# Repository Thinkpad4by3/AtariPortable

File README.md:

# AtariPortable
Atari 2600 new board with Composite and S-Video

Despite the name, it is not a portable yet. It is a remade board from original Atari 2600 schematics but updated for more modern features like proper composite and s-video outputs. Also Made the board physically smaller.

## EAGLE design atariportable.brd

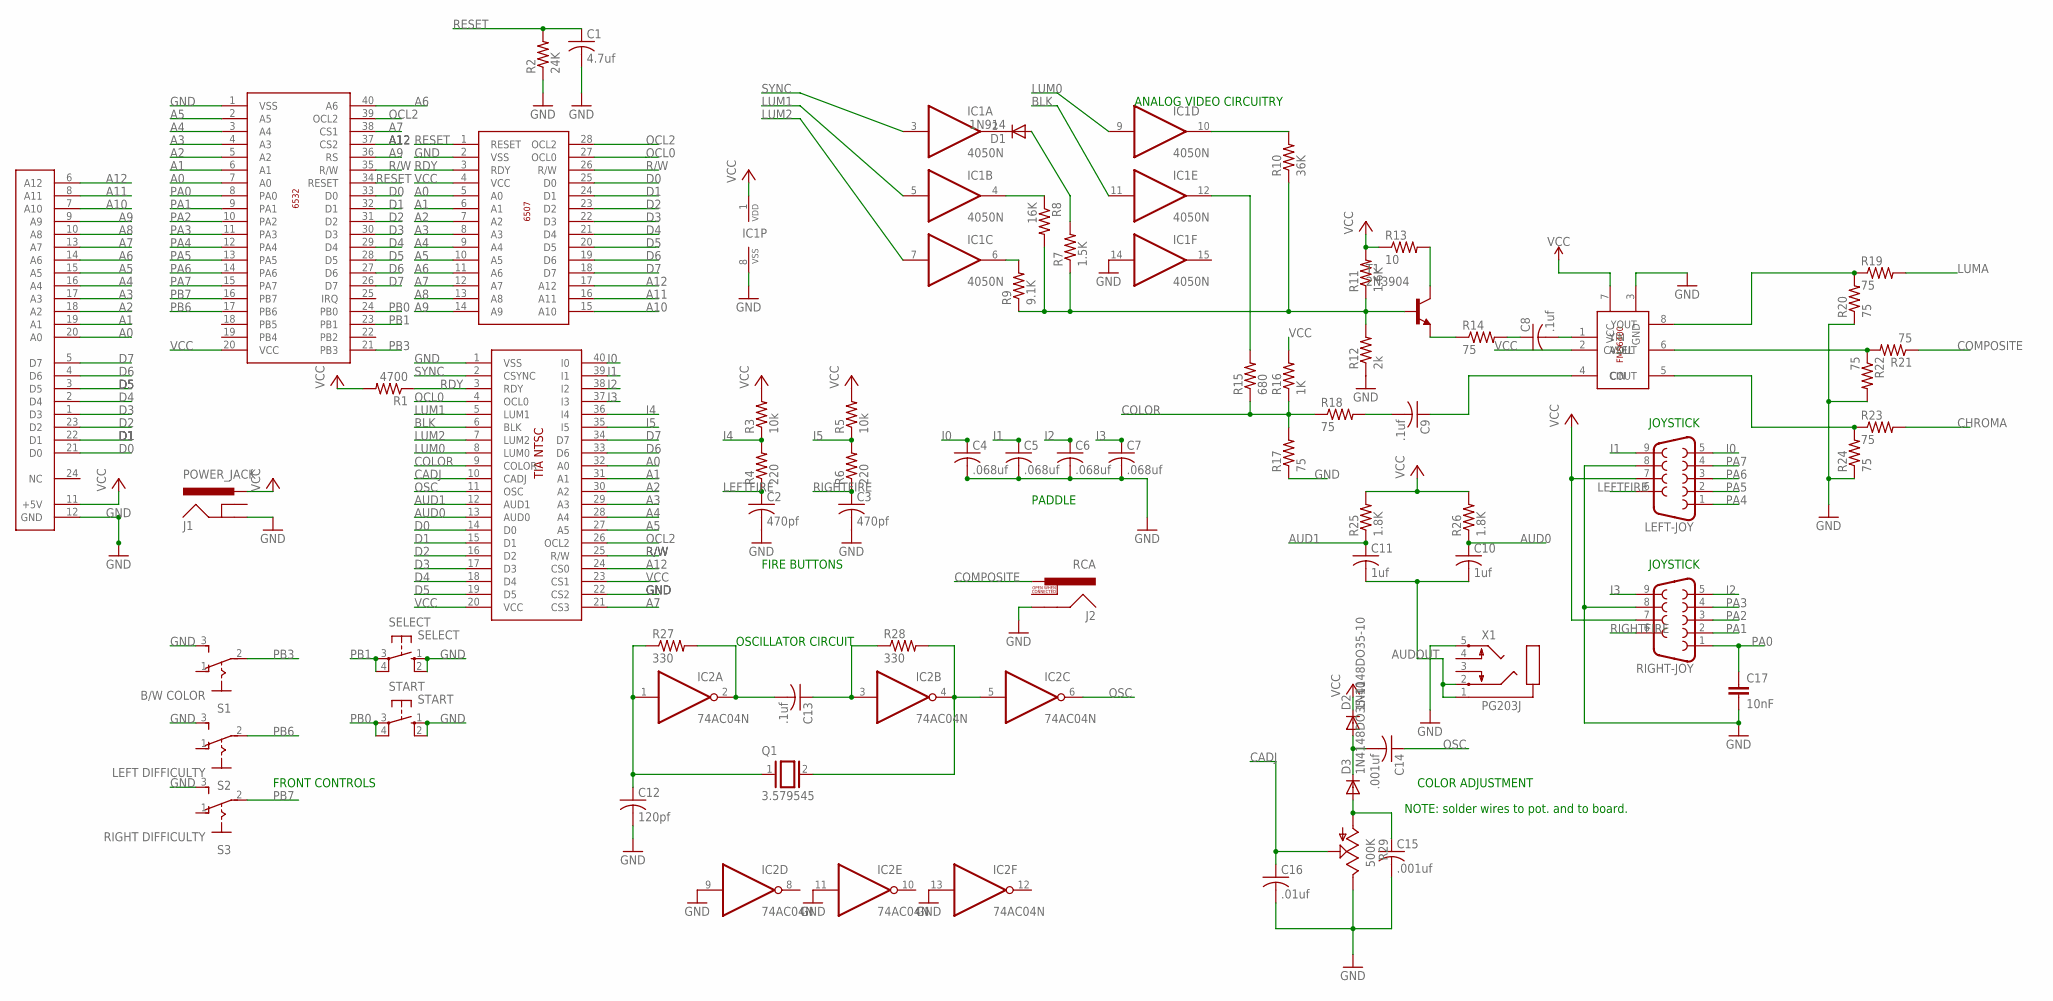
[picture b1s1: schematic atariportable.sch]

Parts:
6507: 6507; DIP28
6532: 6532; DIP40
C1: 4.7uf; C025-030X050
C2, C3: 470pf; C025-050X050
C4, C5, C6, C7: .068uf; C025-024X044
C8, C9: .1uf; C025-025X050
C10, C11: 1uf; C025-050X050
C12: 120pf; C075-042X103
C13: .1uf; C050-050X075
C14, C15: .001uf; C025-050X050
C16: .01uf; C050-055X075
C17: 10nF; C2.5-3
CONN1: 24POSCECARDEDGE; 24POSEDGECARD
D1: 1N914; DO35-10
D2, D3: 1N4148DO35-10; DO35-10
IC1: 4050N; DIL16
IC2: 74AC04N; DIL14
J1: POWER_JACK; POWER_JACK_PTH
J2: RCA
LEFT-JOY: DB9MALE; DB9_MALE
Q1: 3.579545; Q
R1: 4700; 0207/10
R2: 24K; 0207/10
R3, R5: 10k; 0207/10
R4, R6: 220; 0207/10
R7: 1.5K; 0207/10
R8: 16K; 0207/10
R9: 9.1K; 0207/10
R10: 36K; 0207/10
R11: 1.6K; 0207/10
R12: 2k; 0207/10
R13: 10; 0207/10
R14, R17, R18, R19, R20, R21, R22, R23, R24: 75; 0207/10
R15: 680; 0207/10
R16: 1K; 0207/10
R25, R26: 1.8K; 0207/10
R27, R28: 330; 0207/10
R29: 500K; CA6V
RIGHT-JOY: DB9MALE; DB9_MALE
S1: B/W COLOR; M251
S2: LEFT DIFFICULTY; M251
S3: RIGHT DIFFICULTY; M251
SELECT: SELECT; B3F-10XX
START: START; B3F-10XX
T1: 2N3904; TO92
TIA: TIA; DIP40
U$4: FMS6400; SOIC8
X1: PG203J

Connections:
A0: 6507.5 (A0), 6532.7 (A0), CONN1.20 (A0), TIA.32 (A0)
A1: 6507.6 (A1), 6532.6 (A1), CONN1.19 (A1), TIA.31 (A1)
A2: 6507.7 (A2), 6532.5 (A2), CONN1.18 (A2), TIA.30 (A2)
A3: 6507.8 (A3), 6532.4 (A3), CONN1.17 (A3), TIA.29 (A3)
A4: 6507.9 (A4), 6532.3 (A4), CONN1.16 (A4), TIA.28 (A4)
A5: 6507.10 (A5), 6532.2 (A5), CONN1.15 (A5), TIA.27 (A5)
A6: 6507.11 (A6), 6532.40 (A6), CONN1.14 (A6)
A7: 6507.12 (A7), 6532.38 (CS1), CONN1.13 (A7), TIA.21 (CS3)
A8: 6507.13 (A8), CONN1.10 (A8)
A9: 6507.14 (A9), 6532.36 (RS), CONN1.9 (A9)
A10: 6507.15 (A10), CONN1.7 (A10)
A11: 6507.16 (A11), CONN1.8 (A11)
A12: 6507.17 (A12), 6532.37 (CS2), CONN1.6 (A12), TIA.24 (CS0)
AUD0: C10.1, R26.1, TIA.13 (AUD0)
AUD1: C11.1, R25.1, TIA.12 (AUD1)
AUDOUT: C10.2, C11.2, X1.1, X1.2
BLK: IC1.11 (I), TIA.6 (BLK)
CADJ: C16.1, R29.S, TIA.10 (CADJ)
CHROMA: R23.2
COLOR: R15.1, R16.1, R17.2, R18.1, TIA.9 (COLOR)
COMPOSITE: J2.PIN, R21.1
D0: 6507.25 (D0), 6532.33 (D0), CONN1.21 (D0), TIA.14 (D0)
D1: 6507.24 (D1), 6532.32 (D1), CONN1.22 (D1), TIA.15 (D1)
D2: 6507.23 (D2), 6532.31 (D2), CONN1.23 (D2), TIA.16 (D2)
D3: 6507.22 (D3), 6532.30 (D3), CONN1.1 (D3), TIA.17 (D3)
D4: 6507.21 (D4), 6532.29 (D4), CONN1.2 (D4), TIA.18 (D4)
D5: 6507.20 (D5), 6532.28 (D5), CONN1.3 (D5), TIA.19 (D5)
D6: 6507.19 (D6), 6532.27 (D6), CONN1.4 (D6), TIA.33 (D6)
D7: 6507.18 (D7), 6532.26 (D7), CONN1.5 (D7), TIA.34 (D7)
GND: 6507.2 (VSS), 6532.1 (VSS), C1.2, C2.2, C3.2, C4.2, C5.2, C6.2, C7.2, C12.2, C15.2, C16.2, C17.2, CONN1.12 (GND), IC1.8 (VSS), IC1.14 (I), IC2.7 (GND), IC2.9 (I), IC2.11 (I), IC2.13 (I), J1.GND, J2.SHELL, LEFT-JOY.8, R2.1, R12.1, R17.1, R20.1, R22.2, R24.1, R29.E, RIGHT-JOY.8, S1.3 (S), S2.3 (S), S3.3 (S), SELECT.1 (S), SELECT.2 (S1), START.1 (S), START.2 (S1), TIA.1 (VSS), TIA.22 (CS2), U$4.3 (GND), X1.5
I0: C4.1, LEFT-JOY.5, TIA.40 (I0)
I1: C5.1, LEFT-JOY.9, TIA.39 (I1)
I2: C6.1, RIGHT-JOY.5, TIA.38 (I2)
I3: C7.1, RIGHT-JOY.9, TIA.37 (I3)
I4: R3.1, R4.2, TIA.36 (I4)
I5: R5.1, R6.2, TIA.35 (I5)
LEFTFIRE: C2.1, LEFT-JOY.6, R4.1
LUM0: IC1.9 (I), TIA.8 (LUM0)
LUM1: IC1.5 (I), TIA.5 (LUM1)
LUM2: IC1.7 (I), TIA.7 (LUM2)
LUMA: R19.2
unnamed: D1.C, IC1.2 (O)
unnamed: C8.2, U$4.1 (YIN)
unnamed: D1.A, R7.2
unnamed: IC1.4 (O), R8.1
unnamed: IC1.6 (O), R9.2
unnamed: R7.1, R8.2, R9.1, R10.1, R11.1, R12.2, T1.2 (B)
unnamed: IC1.10 (O), R10.2
unnamed: R13.2, T1.1 (C)
unnamed: R14.1, T1.3 (E)
unnamed: C8.1, R14.2
unnamed: IC1.12 (O), R15.2
unnamed: C9.1, U$4.4 (CIN)
unnamed: C9.2, R18.2
unnamed: R19.1, R20.2, U$4.8 (YOUT)
unnamed: R21.2, R22.1, U$4.6 (CVOUT)
unnamed: R23.1, R24.2, U$4.5 (COUT)
unnamed: C12.1, IC2.1 (I), Q1.1, R27.1
unnamed: C13.2, IC2.2 (O), R27.2
unnamed: C13.1, IC2.3 (I), R28.1
unnamed: IC2.4 (O), IC2.5 (I), Q1.2, R28.2
unnamed: C14.2, D2.A, D3.C
unnamed: C15.1, D3.A, R29.A
OCL0: 6507.27 (OCL0), TIA.4 (OCL0)
OCL2: 6507.28 (OCL2), 6532.39 (OCL2), TIA.26 (OCL2)
OSC: C14.1, IC2.6 (O), TIA.11 (OSC)
PA0: 6532.8 (PA0), C17.1, RIGHT-JOY.1
PA1: 6532.9 (PA1), RIGHT-JOY.2
PA2: 6532.10 (PA2), RIGHT-JOY.3
PA3: 6532.11 (PA3), RIGHT-JOY.4
PA4: 6532.12 (PA4), LEFT-JOY.1
PA5: 6532.13 (PA5), LEFT-JOY.2
PA6: 6532.14 (PA6), LEFT-JOY.3
PA7: 6532.15 (PA7), LEFT-JOY.4
PB0: 6532.24 (PB0), START.3, START.4 (P1)
PB1: 6532.23 (PB1), SELECT.3, SELECT.4 (P1)
PB3: 6532.21 (PB3), S1.2
PB6: 6532.17 (PB6), S2.2
PB7: 6532.16 (PB7), S3.2
R/W: 6507.26 (R/W), 6532.35 (R/W), TIA.25 (R/W)
RDY: 6507.3 (RDY), R1.1, TIA.3 (RDY)
RESET: 6507.1 (RESET), 6532.34 (RESET), C1.1, R2.2
RIGHTFIRE: C3.1, R6.1, RIGHT-JOY.6
SYNC: IC1.3 (I), TIA.2 (CSYNC)
VCC: 6507.4 (VCC), 6532.20 (VCC), CONN1.11 (+5V), D2.C, IC1.1 (VDD), IC2.14 (VCC), J1.PWR, LEFT-JOY.7, R1.2, R3.2, R5.2, R11.2, R13.1, R16.2, R25.2, R26.2, RIGHT-JOY.7, TIA.20 (VCC), TIA.23 (CS1), U$4.2 (ASEL), U$4.7 (VCC)

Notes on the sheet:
FIRE BUTTONS
PADDLE
ANALOG VIDEO CIRCUITRY
FRONT CONTROLS
OSCILLATOR CIRCUIT
COLOR ADJUSTMENT
NOTE: solder wires to pot. and to board.
JOYSTICK

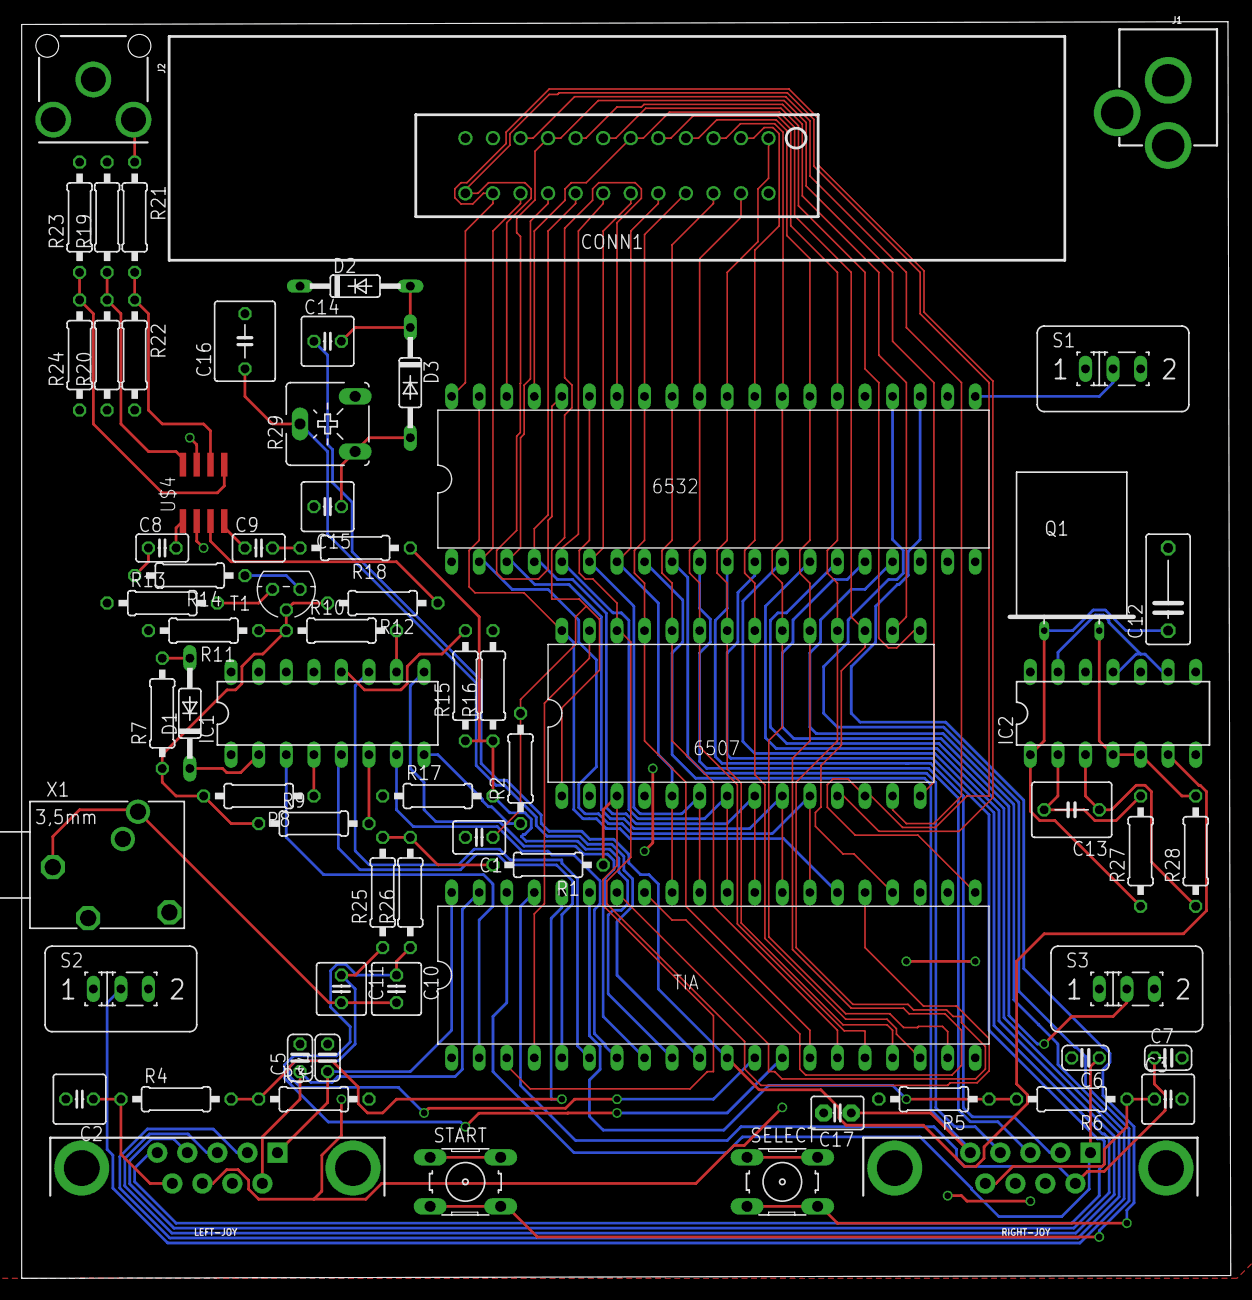
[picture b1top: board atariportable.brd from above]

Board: 2 copper layers, 111.4 x 115.8 mm, 68 parts (0 on the bottom side), 83 nets.

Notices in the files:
parts and their libraries:
SparkFun-Connectors: Licensing: Creative Commons ShareAlike 4.0 International - https://creativecommons.org/licenses/by-sa/4.0
